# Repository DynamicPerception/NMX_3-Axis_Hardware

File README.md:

NMX_3-Axis_Hardware
===================

3-Axis version of the nanoMoCo controller with Bluetooth LE

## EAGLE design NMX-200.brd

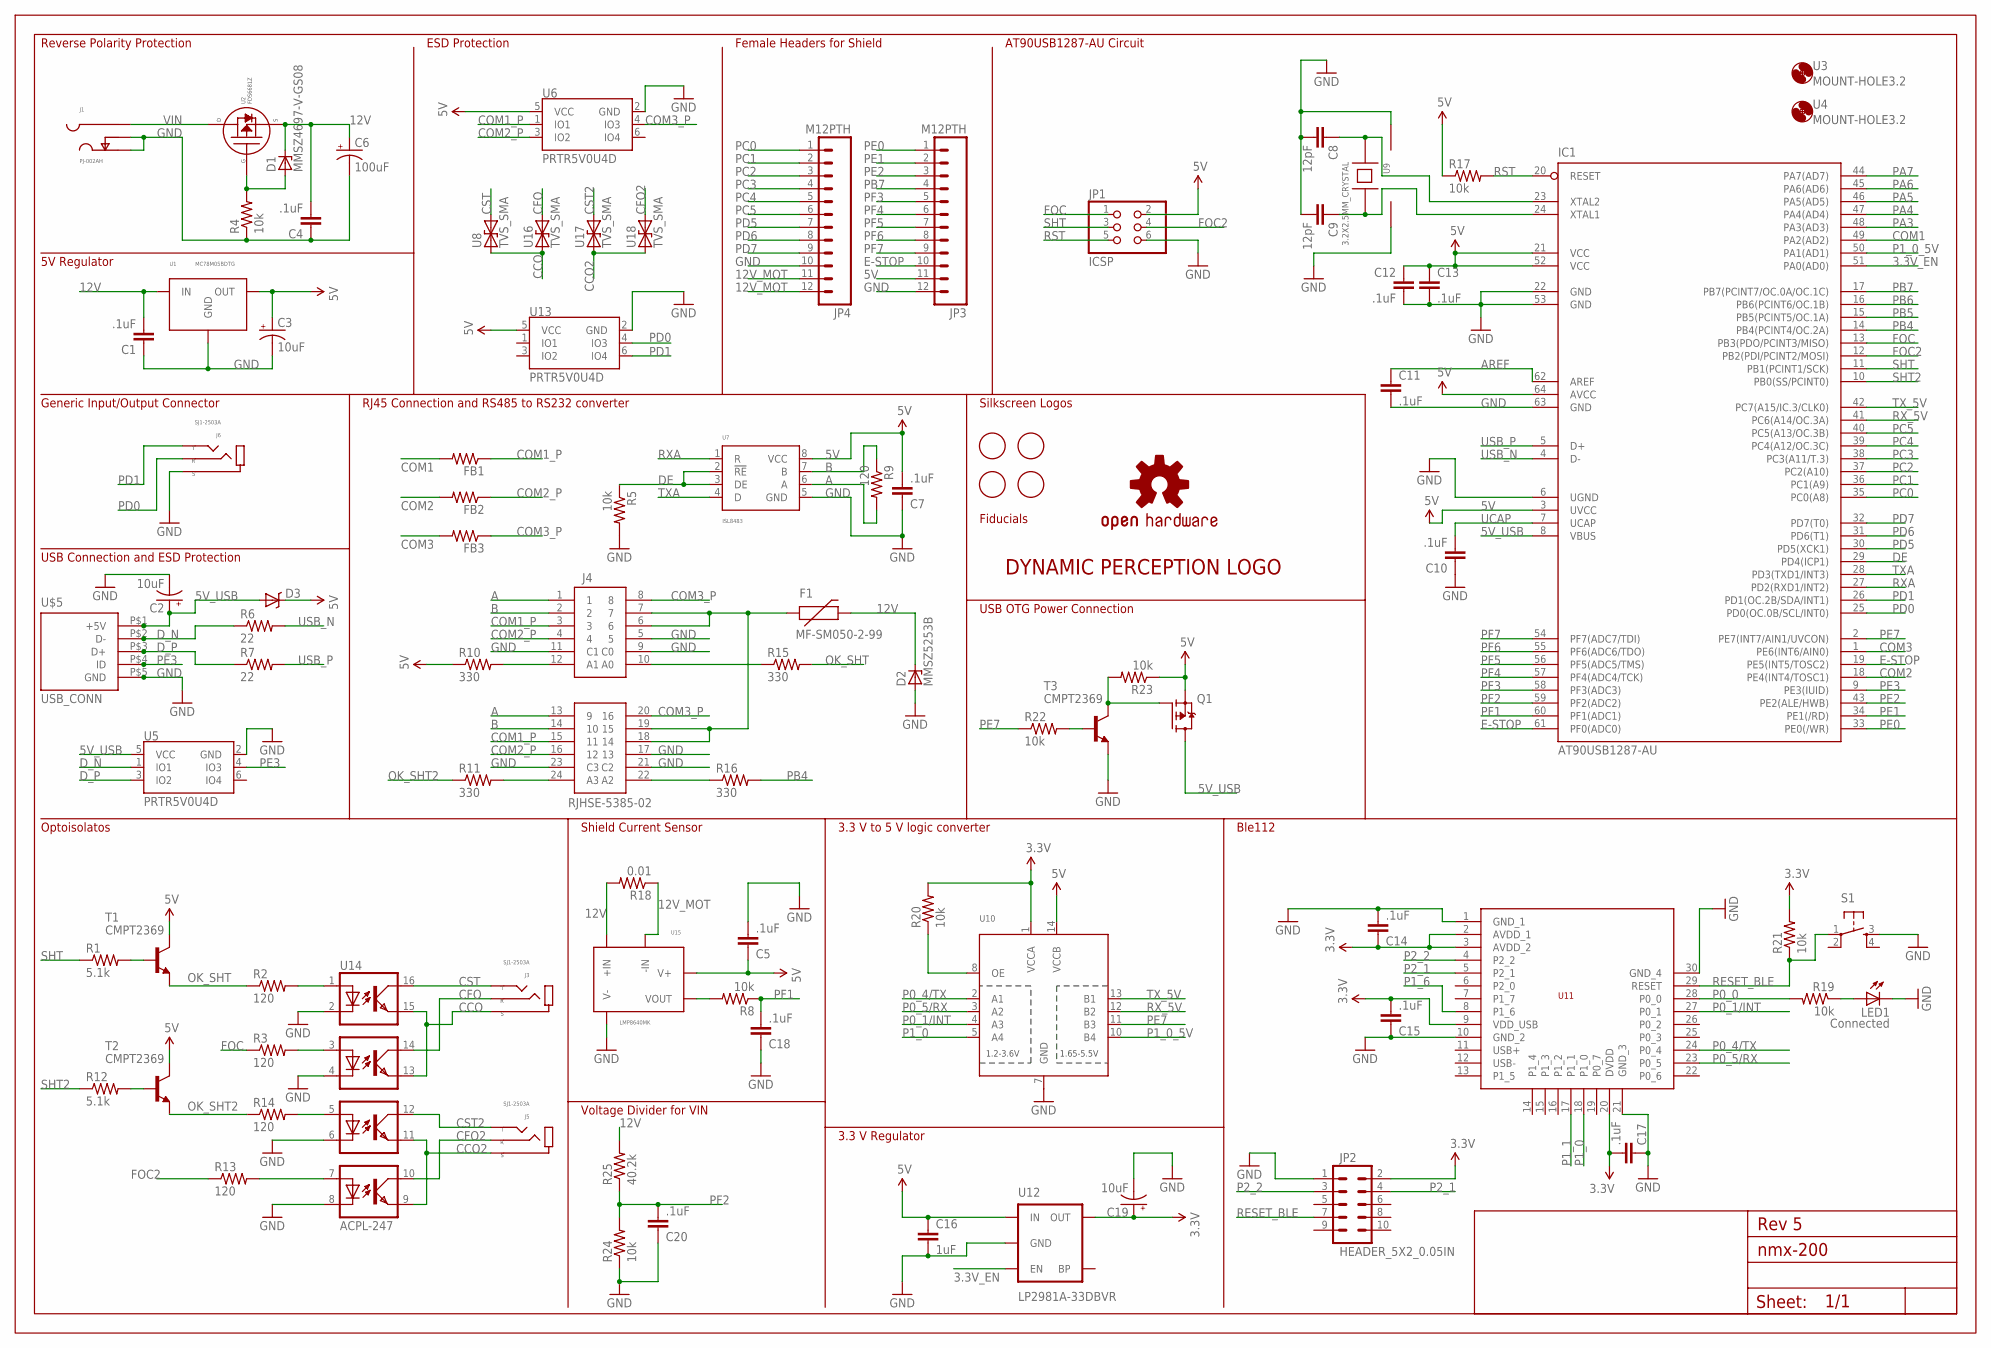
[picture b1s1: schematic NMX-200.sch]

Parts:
C1, C4, C5, C7, C10, C11, C12, C13, C14, C15, C17, C18, C20: .1uF; 0402-CAP; MPN TMK105BJ104KV-F
C2, C3, C19: 10uF; EIA3216; MPN T491A106M016AT
C6: 100uF; PANASONIC_D; MPN EEE-1EA101XP
C8, C9: 12pF; 0402-CAP; MPN C1005C0G1H120J050BA
C16: 1uF; 0402-CAP; MPN C1005X5R1C105K050BC
D1: MMSZ4697-V-GS08; SOD123; MPN MMSZ4697-E3-08
D2: MMSZ5253B; SOD123; MPN MMSZ5253B
D3: DIODE-SCHOTTKY-BAT20J; SOD-323; MPN PMEG3010BEA,115
F1: MF-SM050-2-99; PTC-2920; MPN 0ZCD0050FF2C
FB1, FB2, FB3: HZ0402B102R-10; R0402; MPN HZ0402B102R-10
FRAME2: A3L-LOCSILK_SCREEN; DRAWING_NAME
IC1: AT90USB1287-AU; TQFP64; MPN AT90USB1287-AU
J1: PJ-002AH; DC_JACK_KLDX; MPN PJ-002AH
J3, J5, J6: SJ1-2503A; MPN SJ1-2503A
J4: RJHSE-5385-02; MPN RJHSE-5385-02
JP1: ICSP; 2X03; MPN 67996-406HLF
JP2: HEADER_5X2_0.05IN; MPN 20021121-00010T4LF
JP3, JP4: M12PTH; 1X12; MPN PPTC121LFBN-RC
LED1: Connected; LED-0603; MPN LTST-S270TBKT
Q1: P-CHANNEL_MOSFET; SOT23-3; MPN FDV304P
R1, R12: 5.1k; R0402; MPN RC0402JR-075K1L
R2, R3, R13, R14: 120; R0402; MPN RC0402FR-07180RL
R4, R5, R8, R17, R20, R21, R22, R23, R24: 10k; R0402; MPN RC0402FR-0710KL
R6, R7: 22; R0402; MPN RC0402JR-0722RL
R9: 120; R0402; MPN RC0402JR-07120RL
R10, R11, R15, R16: 330; R0402; MPN RC0402FR-07330RL
R18: 0.01; R1206; MPN RLP73V2BR010JTD
R19: 10k; R0402; MPN RC0402FR-0714KL
R25: 40.2k; R0402; MPN RC0402FR-0740K2L
S1: TAC_SWITCH; TACTICLE_SWITCH_SMD_EVQP0_BOT; MPN EVQ-P0Q02Q
T1, T2: CMPT2369; SOT23-BEC; MPN 2SD1757KT146Q
T3: CMPT2369; SOT23-BEC; MPN BC847BMTF
U1: MC78M05BDTG; DPAK-3; MPN MC78M05BDTRKG
U2: FDS6681Z; DSO-8; MPN FDS6681Z
U3, U4: MOUNT-HOLE3.2; 3,2
U5, U6, U13: PRTR5V0U4D; SOT23-6; MPN PRTR5V0U4D
U7: ISL8483; SO-08; MPN SN65176BD
U8, U16, U17, U18: TVS_SMA; SMA_DIODE; MPN SMAJ48CA
U9: 3.2X2.5MM_CRYSTAL; 3.2X2.5MM; MPN CX3225SB16000E0FPZ25
U10: TXB0104PWR; TSSOP14; MPN TXB0104PWR
U11: BLE112; BLE112-A; MPN BLE112-A-V1
U12: LP2981A-33DBVR; SOT23-5; MPN LP2981A-33DBVR
U14: ACPL-247; 16-SOIC; MPN ACPL-247-500E
U15: LMP8640MK; 6-SOT; MPN LMP8640MK-H/NOPB
U$1: DP_LOGOMICRO; DP_LOGO_MICRO
U$2: OSHW-LOGOS; OSHW-LOGO-S
U$3, U$4, U$6, U$7: FIDUCIAL; FIDUCIAL_1MM
U$5: USB_CONN; 10118194-0001LF

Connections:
3.3V: C14.1, C15.2, C17.2, C19.A (+), JP2.2, R20.2, R21.2, U10.1 (VCCA), U11.2 (AVDD_1), U11.3 (AVDD_2), U11.9 (VDD_USB), U11.20 (DVDD), U12.5 (OUT)
3.3V_EN: IC1.51 (PA0(AD0)), U12.3 (EN)
5V: C3.A (+), C5.1, C7.2, C12.1, C13.1, C16.1, D3.C, IC1.3 (UVCC), IC1.21 (VCC), IC1.52 (VCC), IC1.64 (AVCC), JP1.2, JP3.11, Q1.S, R10.1, R17.1, R23.1, T1.C, T2.C, U1.2 (OUT), U6.5 (VCC), U7.8 (VCC), U10.14 (VCCB), U12.1 (IN), U13.5 (VCC), U15.6 (V+)
5V_USB: C2.A (+), D3.A, IC1.8 (VBUS), Q1.D, U5.5 (VCC), U$5.P$1 (+5V)
12V: C1.2, C4.2, C6.+, D1.C, D2.C, F1.P$2 (2), R18.2, R25.2, U1.1 (IN), U2.1 (SOURCE), U2.2 (SOURCE), U2.3 (SOURCE), U15.3 (+IN)
12V_MOT: JP4.11, JP4.12, R18.1, U15.4 (-IN)
A: J4.1, J4.13 (9), R9.2, U7.6 (A)
AREF: C11.1, IC1.62 (AREF)
B: J4.2, J4.14 (10), R9.1, U7.7 (B)
CCO: J3.1 (S), U8.C (1), U14.13, U14.15, U16.C (1)
CCO2: J5.1 (S), U14.9, U14.11, U17.C (1), U18.C (1)
CFO: J3.4 (R), U14.14, U16.A (2)
CFO2: J5.4 (R), U14.10, U18.A (2)
COM1: FB1.2, IC1.49 (PA2(AD2))
COM1_P: FB1.1, J4.3, J4.15 (11), U6.1 (IO1)
COM2: FB2.2, IC1.18 (PE4(INT4/TOSC1))
COM2_P: FB2.1, J4.4, J4.16 (12), U6.3 (IO2)
COM3: FB3.2, IC1.1 (PE6(INT6/AIN0))
COM3_P: FB3.1, J4.8, J4.20 (16), U6.4 (IO3)
CST: J3.2 (T), J3.3 (T), U8.A (2), U14.16
CST2: J5.2 (T), J5.3 (T), U14.12, U17.A (2)
DE: IC1.29 (PD4(ICP1)), R5.1, U7.2 (!RE), U7.3 (DE)
D_N: R6.1, U5.1 (IO1), U$5.P$2 (D-)
D_P: R7.1, U5.3 (IO2), U$5.P$3 (D+)
E-STOP: IC1.19 (PE5(INT5/TOSC2)), IC1.61 (PF0(ADC0)), JP3.10
FOC: IC1.13 (PB3(PDO/PCINT3/MISO)), JP1.1, R3.1
FOC2: IC1.12 (PB2(PDI/PCINT2/MOSI)), JP1.4, R13.1
GND: C1.1, C2.C (-), C3.C (-), C4.1, C5.2, C6.-, C7.1, C8.2, C9.2, C10.1, C11.2, C12.2, C13.2, C14.2, C15.1, C16.2, C17.1, C18.1, C19.C (-), C20.1, D2.A, IC1.6 (UGND), IC1.22 (GND), IC1.53 (GND), IC1.63 (GND), J1.GND (SLEEVE), J1.GNDBREAK (SLEEVE_SHUNT), J4.5, J4.9 (C0), J4.11 (C1), J4.17 (13), J4.21 (C2), J4.23 (C3), J6.1 (S), JP1.6, JP2.1, JP3.12, JP4.10, LED1.C, R4.1, R5.2, R24.1, S1.3, T3.E, U1.4 (GND), U5.2 (GND), U6.2 (GND), U7.5 (GND), U9.2 (GND), U9.4, U10.7 (GND), U11.1 (GND_1), U11.10 (GND_2), U11.21 (GND_3), U11.30 (GND_4), U12.2 (GND), U13.2 (GND), U14.2, U14.4, U14.6, U14.8, U15.2 (V-), U$5.P$5 (GND)
unnamed: R20.1, U10.8 (OE)
unnamed: R22.2, T3.B
unnamed: LED1.A, R19.1
unnamed: J4.10 (A0), R15.1
unnamed: D1.A, R4.2, U2.4 (GATE)
unnamed: R2.2, U14.1
unnamed: R3.2, U14.3
unnamed: R8.2, U15.1 (VOUT)
unnamed: R14.2, U14.5
unnamed: R13.2, U14.7
unnamed: J4.12 (A1), R10.2
unnamed: J4.24 (A3), R11.2
unnamed: Q1.G, R23.2, T3.C
unnamed: J4.22 (A2), R16.1
unnamed: F1.P$1 (1), J4.6, J4.7, J4.18 (14), J4.19 (15)
unnamed: R1.2, T1.B
unnamed: R12.2, T2.B
OK_SHT: R2.1, R15.2, T1.E
OK_SHT2: R11.1, R14.1, T2.E
P0_0: R19.2, U11.28 (P0_0)
P0_1/INT: U10.4 (A3), U11.27 (P0_1)
P0_4/TX: U10.2 (A1), U11.24 (P0_4)
P0_5/RX: U10.3 (A2), U11.23 (P0_5)
P1_0: U10.5 (A4), U11.18 (P1_0)
P1_0_5V: IC1.50 (PA1(AD1)), U10.10 (B4)
P1_1: U11.17 (P1_1)
P1_6: U11.8 (P1_6)
P2_1: JP2.4, U11.5 (P2_1)
P2_2: JP2.3, U11.4 (P2_2)
PA3: IC1.48 (PA3(AD3))
PA4: IC1.47 (PA4(AD4))
PA5: IC1.46 (PA5(AD5))
PA6: IC1.45 (PA6(AD6))
PA7: IC1.44 (PA7(AD7))
PB4: IC1.14 (PB4(PCINT4/OC.2A)), R16.2
PB5: IC1.15 (PB5(PCINT5/OC.1A))
PB6: IC1.16 (PB6(PCINT6/OC.1B))
PB7: IC1.17 (PB7(PCINT7/OC.0A/OC.1C)), JP3.4
PC0: IC1.35 (PC0(A8)), JP4.1
PC1: IC1.36 (PC1(A9)), JP4.2
PC2: IC1.37 (PC2(A10)), JP4.3
PC3: IC1.38 (PC3(A11/T.3)), JP4.4
PC4: IC1.39 (PC4(A12/OC.3C)), JP4.5
PC5: IC1.40 (PC5(A13/OC.3B)), JP4.6
PD0: IC1.25 (PD0(OC.0B/SCL/INT0)), J6.4 (R), U13.4 (IO3)
PD1: IC1.26 (PD1(OC.2B/SDA/INT1)), J6.2 (T), J6.3 (T), U13.6 (IO4)
PD5: IC1.30 (PD5(XCK1)), JP4.7
PD6: IC1.31 (PD6(T1)), JP4.8
PD7: IC1.32 (PD7(T0)), JP4.9
PE0: IC1.33 (PE0(/WR)), JP3.1
PE1: IC1.34 (PE1(/RD)), JP3.2
PE2: IC1.43 (PE2(ALE/HWB)), JP3.3
PE3: IC1.9 (PE3(IUID)), U5.4 (IO3), U$5.P$4 (ID)
PE7: IC1.2 (PE7(INT7/AIN1/UVCON)), R22.1, U10.11 (B3)
PF1: C18.2, IC1.60 (PF1(ADC1)), R8.1
PF2: C20.2, IC1.59 (PF2(ADC2)), R24.2, R25.1
PF3: IC1.58 (PF3(ADC3)), JP3.5
PF4: IC1.57 (PF4(ADC4/TCK)), JP3.6
PF5: IC1.56 (PF5(ADC5/TMS)), JP3.7
PF6: IC1.55 (PF6(ADC6/TDO)), JP3.8
PF7: IC1.54 (PF7(ADC7/TDI)), JP3.9
RESET_BLE: JP2.7, R21.1, S1.1, U11.29 (RESET)
RST: IC1.20 (RESET), JP1.5, R17.2
RXA: IC1.27 (PD2(RXD1/INT2)), U7.1 (R)
RX_5V: IC1.41 (PC6(A14/OC.3A)), U10.12 (B2)
SHT: IC1.11 (PB1(PCINT1/SCK)), JP1.3, R1.1
SHT2: IC1.10 (PB0(SS/PCINT0)), R12.1
TXA: IC1.28 (PD3(TXD1/INT3)), U7.4 (D)
TX_5V: IC1.42 (PC7(A15/IC.3/CLK0)), U10.13 (B1)
UCAP: C10.2, IC1.7 (UCAP)
USB_N: IC1.4 (D-), R6.2
USB_P: IC1.5 (D+), R7.2
VIN: J1.PWR (PIN), U2.5 (DRAIN), U2.6 (DRAIN), U2.7 (DRAIN), U2.8 (DRAIN)
XTAL1: C9.1, IC1.24 (XTAL1), U9.3
XTAL2: C8.1, IC1.23 (XTAL2), U9.1

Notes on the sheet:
Ble112
3.3 V to 5 V logic converter
3.3 V Regulator
Optoisolatos
Reverse Polarity Protection
5V Regulator
Generic Input/Output Connector
USB Connection and ESD Protection
RJ45 Connection and RS485 to RS232 converter
ESD Protection
Female Headers for Shield
AT90USB1287-AU Circuit
Shield Current Sensor
Voltage Divider for VIN
USB OTG Power Connection
Silkscreen Logos
Fiducials
Rev 5

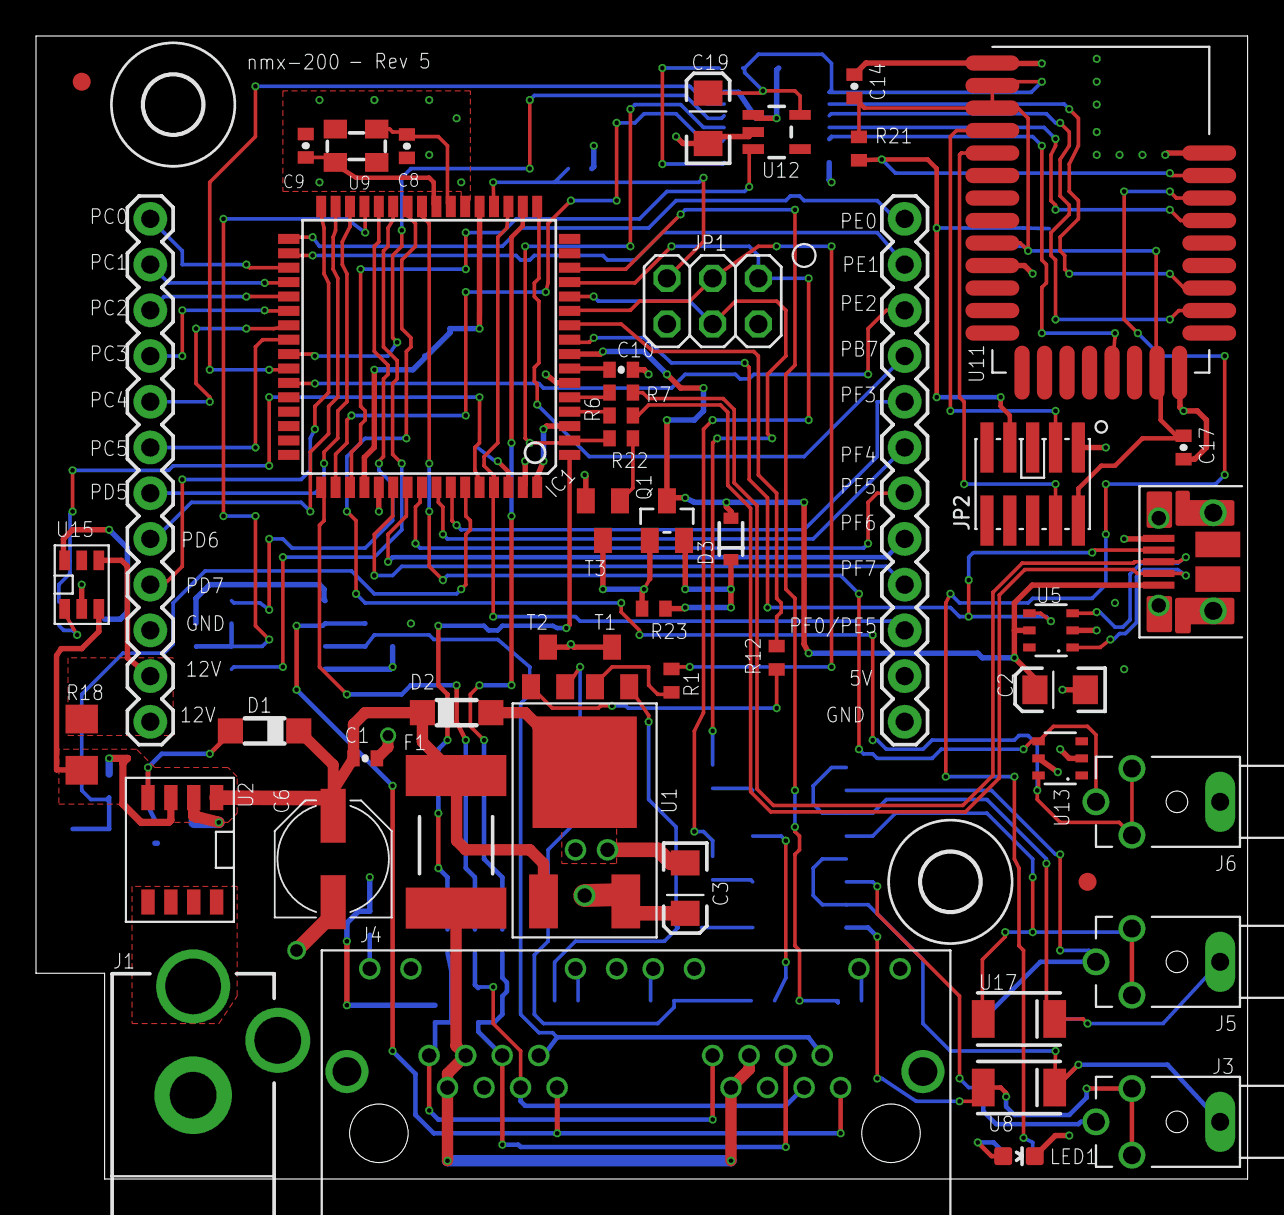
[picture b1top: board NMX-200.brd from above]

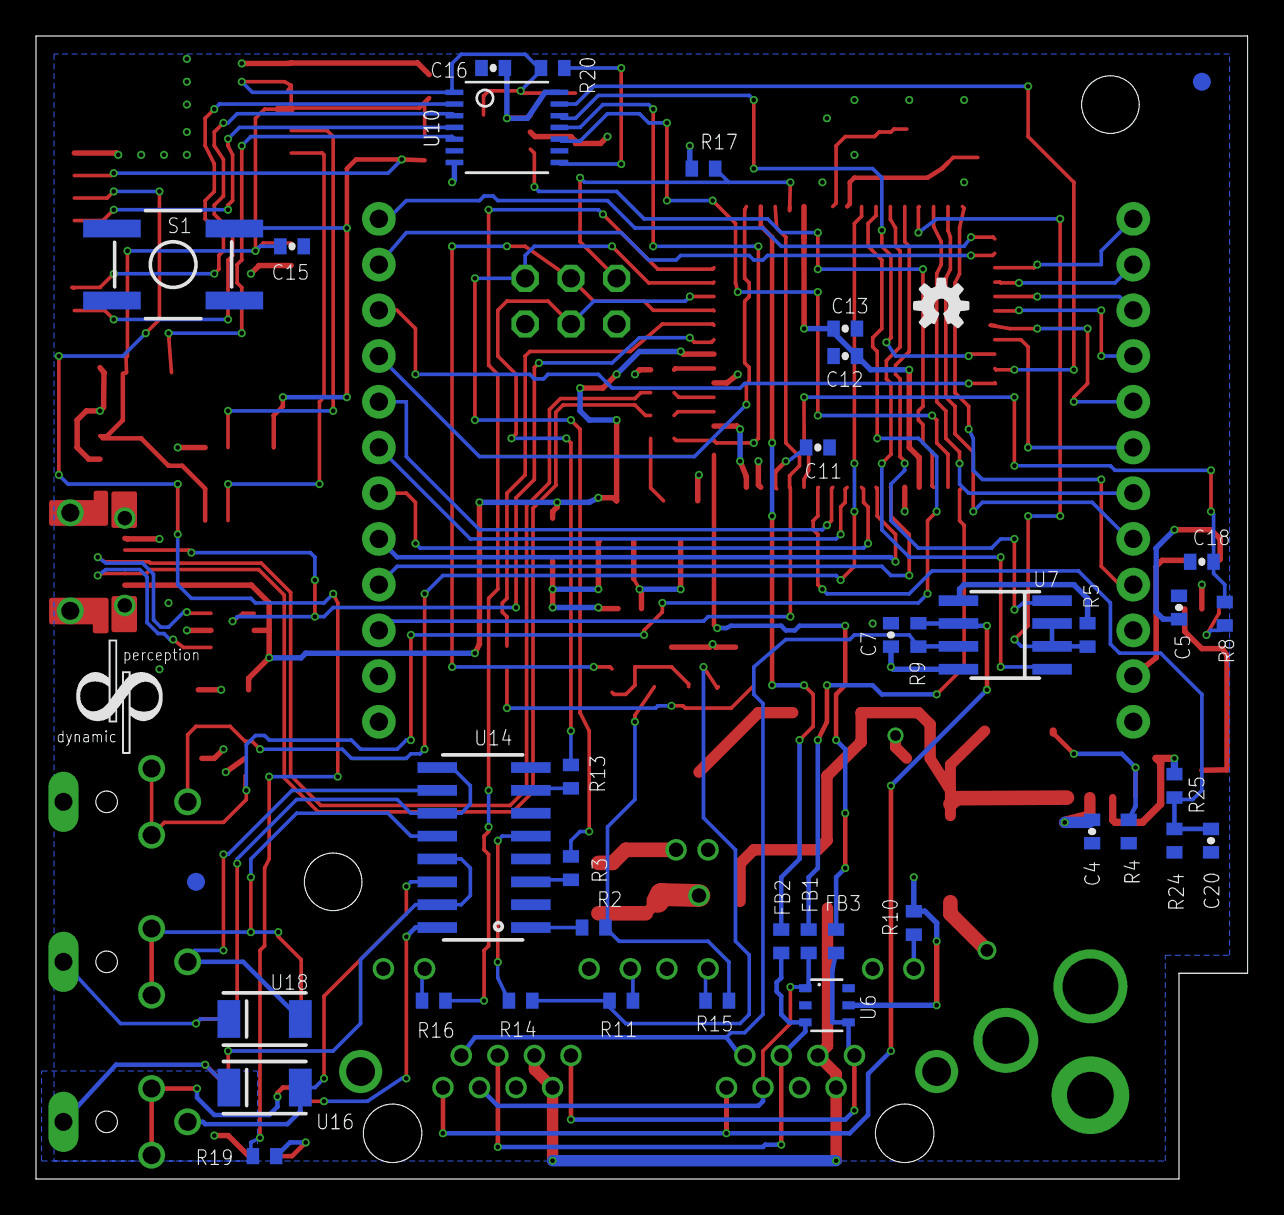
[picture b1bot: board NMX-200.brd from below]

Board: 4 copper layers, 67.3 x 63.5 mm, 94 parts (40 on the bottom side), 94 nets.

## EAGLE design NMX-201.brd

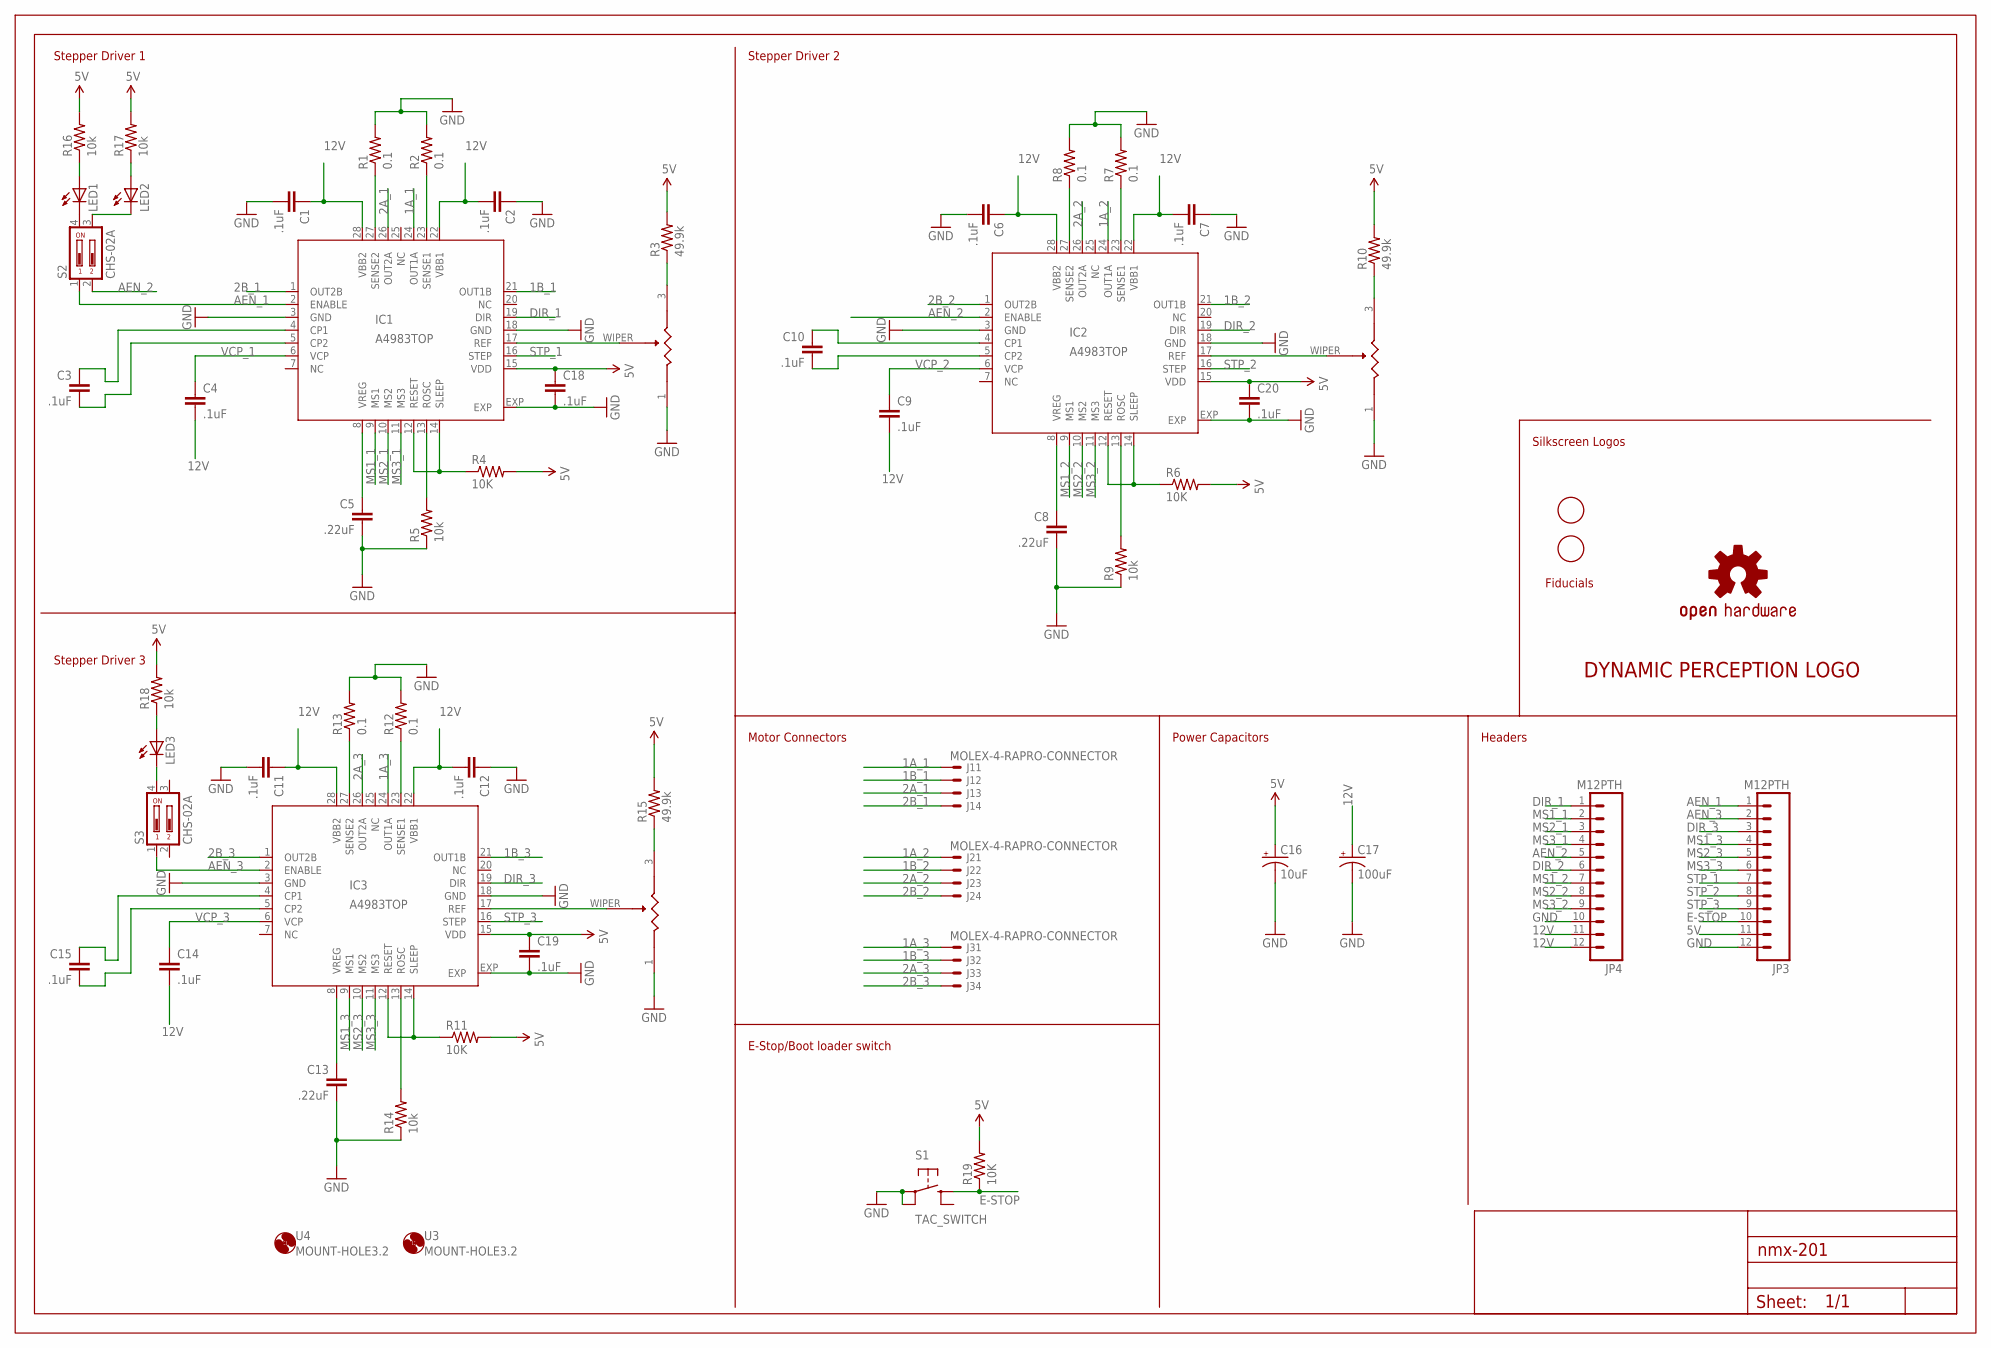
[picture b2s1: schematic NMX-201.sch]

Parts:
C1, C2, C3, C4, C6, C7, C9, C10, C11, C12, C14, C15, C18, C19, C20: .1uF; 0402-CAP; MPN TMK105BJ104KV-F
C5, C8, C13: .22uF; 0402-CAP; MPN TMK105BJ224KVHF
C16: 10uF; EIA3216; MPN T491A106M016AT
C17: 100uF; PANASONIC_D; MPN EEE-1EA101XP
FRAME2: A3L-LOCSILK_SCREEN; DRAWING_NAME
IC1, IC2, IC3: A4983TOP; QFN28ET; MPN A4983SETTR-T
J1, J2, J3: MOLEX-4-RAPRO-CONNECTOR; PRO_CONNECTOR; MPN 0022053041
JP3, JP4: M12PTH; 1X12; MPN 0901200132
LED1, LED2, LED3: LED0603; LED-0603; MPN LB Q39G-L2N2-35-1
R1, R2, R7, R8, R12, R13: 0.1; R0603; MPN RU1608FR100CS
R3, R10, R15: 49.9k; R0402_BOTTOM; MPN RC0402FR-0749K9L
R4, R6, R11, R19: 10K; R0402_BOTTOM; MPN RC0402FR-0710KL
R5, R9, R14: 10k; R0402_BOTTOM; MPN RC0402FR-0720KL
R16, R17, R18: 10k; R0402_BOTTOM; MPN RC0402FR-0714KL
S1: TAC_SWITCH; TAC_SWITCH_THR; MPN 2-1825027-0
S2, S3: CHS-02A
U1, U2, U5: CADJ; 3MM_SMD; MPN TC33X-2-103E
U3, U4: MOUNT-HOLE3.2; 3,2
U$1: DP_LOGOMICRO; DP_LOGO_MICRO
U$2: OSHW-LOGOS; OSHW-LOGO-S
U$3, U$4: FIDUCIAL; FIDUCIAL_1MM

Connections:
1A_1: IC1.24 (OUT1A), J1.P$1
1A_2: IC2.24 (OUT1A), J2.P$1
1A_3: IC3.24 (OUT1A), J3.P$1
1B_1: IC1.21 (OUT1B), J1.P$2
1B_2: IC2.21 (OUT1B), J2.P$2
1B_3: IC3.21 (OUT1B), J3.P$2
2A_1: IC1.26 (OUT2A), J1.P$3
2A_2: IC2.26 (OUT2A), J2.P$3
2A_3: IC3.26 (OUT2A), J3.P$3
2B_1: IC1.1 (OUT2B), J1.P$4
2B_2: IC2.1 (OUT2B), J2.P$4
2B_3: IC3.1 (OUT2B), J3.P$4
5V: C16.A (+), C18.1, C19.1, C20.1, IC1.15 (VDD), IC2.15 (VDD), IC3.15 (VDD), JP3.11, R3.2, R4.2, R6.2, R10.2, R11.2, R15.2, R16.2, R17.2, R18.2, R19.2
12V: C1.1, C2.2, C4.2, C6.1, C7.2, C9.2, C11.1, C12.2, C14.2, C17.+, IC1.22 (VBB1), IC1.28 (VBB2), IC2.22 (VBB1), IC2.28 (VBB2), IC3.22 (VBB1), IC3.28 (VBB2), JP4.11, JP4.12
AEN_1: IC1.2 (ENABLE), JP3.1, S2.1
AEN_2: IC2.2 (ENABLE), JP4.5, S2.2
AEN_3: IC3.2 (ENABLE), JP3.2, S3.1
ARST1: IC1.12 (RESET), IC1.14 (SLEEP), R4.1
ARST2: IC2.12 (RESET), IC2.14 (SLEEP), R6.1
ARST3: IC3.12 (RESET), IC3.14 (SLEEP), R11.1
DIR_1: IC1.19 (DIR), JP4.1
DIR_2: IC2.19 (DIR), JP4.6
DIR_3: IC3.19 (DIR), JP3.3
E-STOP: JP3.10, R19.1, S1.B (3)
GND: C1.2, C2.1, C5.2, C6.2, C7.1, C8.2, C11.2, C12.1, C13.2, C16.C (-), C17.-, C18.2, C19.2, C20.2, IC1.3 (GND), IC1.18 (GND), IC1.EXP, IC2.3 (GND), IC2.18 (GND), IC2.EXP, IC3.3 (GND), IC3.18 (GND), IC3.EXP, JP3.12, JP4.10, R1.2, R2.2, R5.1, R7.2, R8.2, R9.1, R12.2, R13.2, R14.1, S1.A (1), S1.P$1 (2), U1.1, U2.1, U5.1
MS1_1: IC1.9 (MS1), JP4.2
MS1_2: IC2.9 (MS1), JP4.7
MS1_3: IC3.9 (MS1), JP3.4
MS2_1: IC1.10 (MS2), JP4.3
MS2_2: IC2.10 (MS2), JP4.8
MS2_3: IC3.10 (MS2), JP3.5
MS3_1: IC1.11 (MS3), JP4.4
MS3_2: IC2.11 (MS3), JP4.9
MS3_3: IC3.11 (MS3), JP3.6
unnamed: C10.1, IC2.4 (CP1)
unnamed: C10.2, IC2.5 (CP2)
unnamed: IC2.23 (SENSE1), R7.1
unnamed: IC2.27 (SENSE2), R8.1
unnamed: IC2.17 (REF), U2.WIPER (2)
unnamed: R10.1, U2.3
unnamed: C15.1, IC3.4 (CP1)
unnamed: C15.2, IC3.5 (CP2)
unnamed: IC3.23 (SENSE1), R12.1
unnamed: IC3.27 (SENSE2), R13.1
unnamed: IC3.17 (REF), U5.WIPER (2)
unnamed: R15.1, U5.3
unnamed: LED1.A, R16.1
unnamed: LED2.A, R17.1
unnamed: LED3.A, R18.1
unnamed: LED1.C, S2.4
unnamed: LED2.C, S2.3
unnamed: LED3.C, S3.4
unnamed: C3.1, IC1.4 (CP1)
unnamed: C3.2, IC1.5 (CP2)
unnamed: IC1.23 (SENSE1), R2.1
unnamed: IC1.27 (SENSE2), R1.1
unnamed: IC1.17 (REF), U1.WIPER (2)
unnamed: R3.1, U1.3
ROSC1: IC1.13 (ROSC), R5.2
ROSC2: IC2.13 (ROSC), R9.2
ROSC3: IC3.13 (ROSC), R14.2
STP_1: IC1.16 (STEP), JP3.7
STP_2: IC2.16 (STEP), JP3.8
STP_3: IC3.16 (STEP), JP3.9
VCP_1: C4.1, IC1.6 (VCP)
VCP_2: C9.1, IC2.6 (VCP)
VCP_3: C14.1, IC3.6 (VCP)
VREG1: C5.1, IC1.8 (VREG)
VREG2: C8.1, IC2.8 (VREG)
VREG3: C13.1, IC3.8 (VREG)

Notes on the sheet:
Stepper Driver 1
Stepper Driver 2
Stepper Driver 3
Motor Connectors
E-Stop/Boot loader switch
Headers
Power Capacitors
Silkscreen Logos
Fiducials

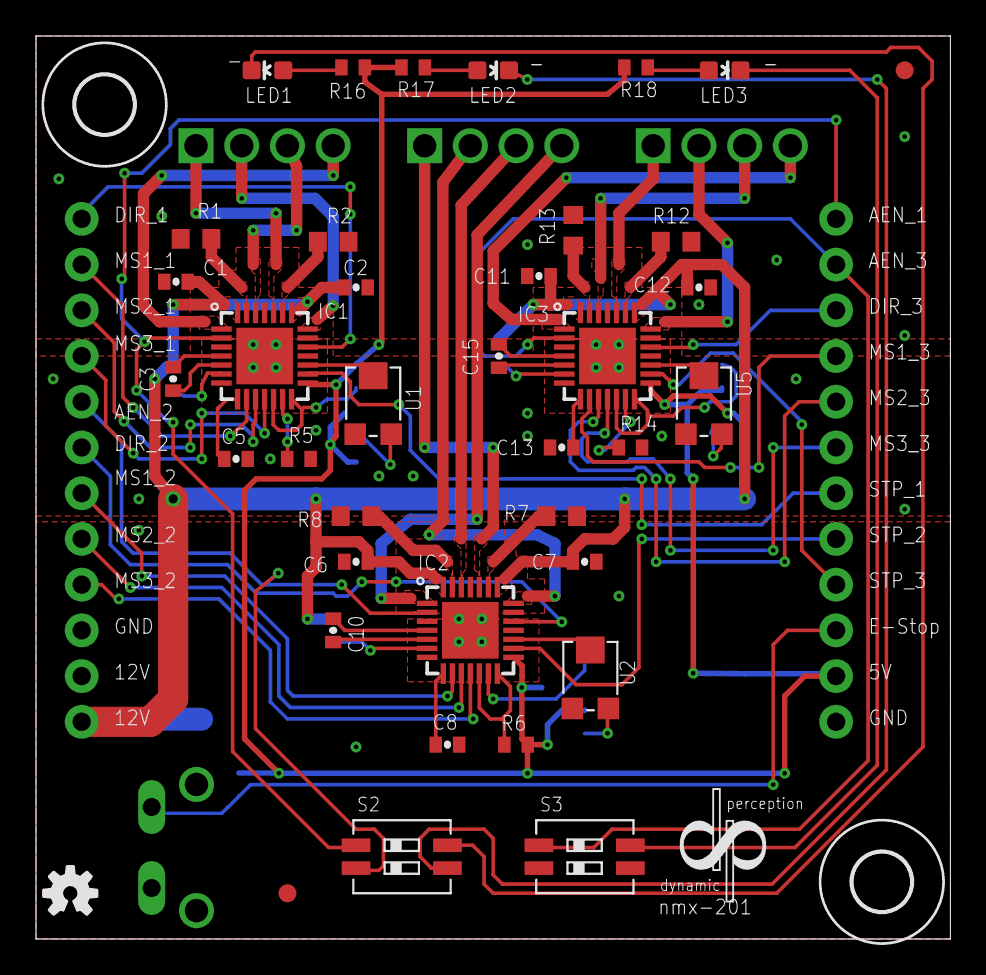
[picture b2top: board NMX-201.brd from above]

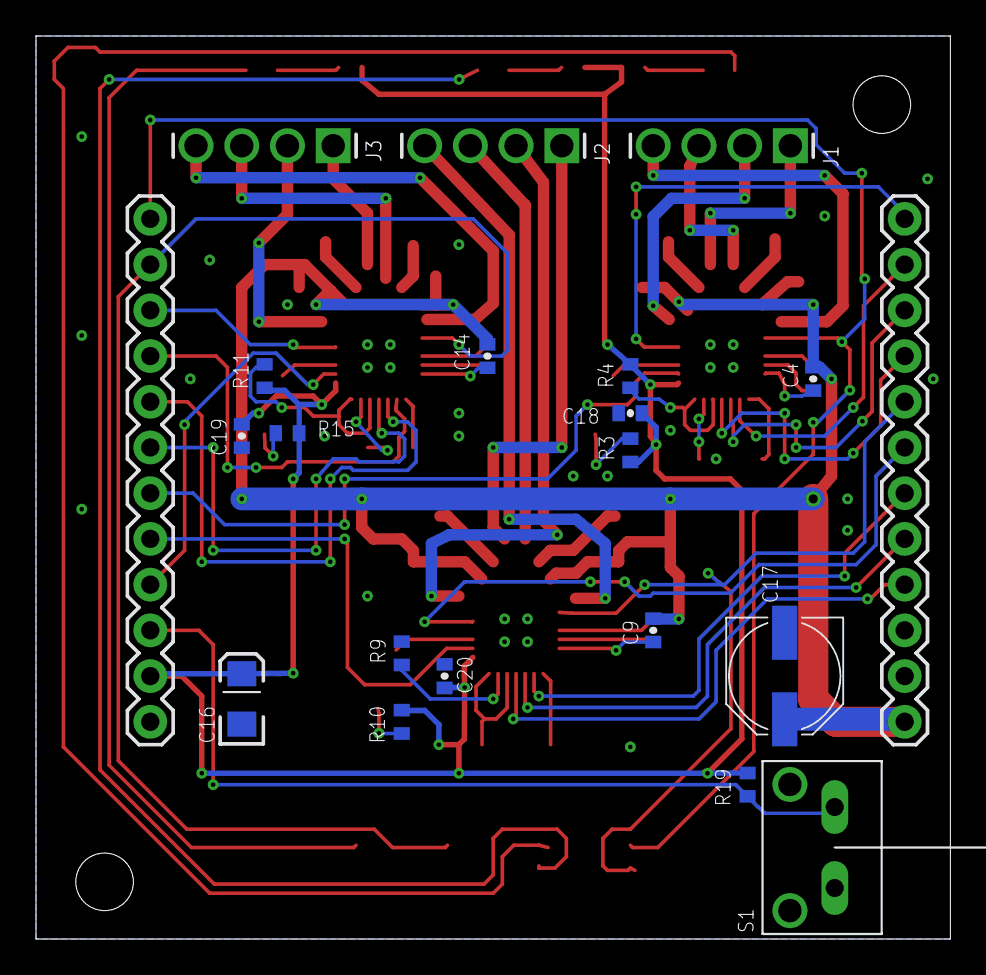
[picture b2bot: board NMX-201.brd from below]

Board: 2 copper layers, 50.8 x 50.2 mm, 63 parts (20 on the bottom side), 70 nets.

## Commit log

2014-08-26 Initial GitHub upload - 8/26/14
    To do:
    --Update ESD suppressors on phototransistors from 5V to 80V limit.
    --Change trace width from .024 to .025 on all traces from motor headers
2014-08-27 Board Updates
    Changed TVS diodes for isolated jack for 200, changed a few traces in
    201
2014-08-27 Added .gitignore
    Ignores backup files and CAM files. If you want to upload CAM files, zip
    them first and upload them as a bundle.
2014-08-27 Deleted backup files that should have been ignored
2014-08-27 Updated TVS Attributes
2014-08-27 Fixed NMX-200 schematic typo
    Two 10k resistors were marked with an upper case "K" instead of lower
    case k", which caused them to appear as a separate line on the exported
    BOM.
2014-08-27 Upload of fabrication data
    Upload of ZIP files containing Gerber files, BOMs, and assembly drawings
    for each board.
2014-08-27 Fixed fabrication data upload
    Accidentally uploaded the NMX-200 CAM zip instead of the NMX-201
    fabrication zip. Also unzipped everything in those files and put them in
    normal folders.
2014-08-27 Removed extraneous zip files
    Oops, forgot to remove these
2014-09-30 Changed silkscreen to indicate polarity of some components
2014-10-03 Update to Silk Screen
2014-10-03 Update Silk Screen
2015-01-23 Replaced 5V regulator with cold-resistant model
    The MC78M05CDTG ON-Semiconductor regulator was replaced with the
    MC78M05BDTG. The minimum operating temperature of former is 0°C and the
    latter is -45°C. There have been issues connecting to the NMX via
    Bluetooth when it is very cold, so this change is being made in an
    attempt to address that issue.
    The CAM files have not changed at all, but their names have been updated
2016-03-18 Added NMX-201-B
2016-03-18 Added NMX-200 and NMX-201 schematic PDFs
2016-08-18 Changed NMX 200 to 4 layer design
2016-08-19 Fixed broken route, moved oscilator caps to top layer
2016-08-23 Added DIP switches and increased LED resistor vals
    NMX 201-B:
    - Added switches to allow users to turn off motor movement indicator
    LEDs.
    - Changed R16, R17, R19 to 14k resistances in order to reduce LED
    brightness.
2016-08-23 Updated NMX-201 to match NMX-201B
    The only difference between NMX-201 and NMX-201B is whether the the
    component attached to the motor connector ports is a screw terminal or a
    Molex connector, so there's really no need to maintain two different
    schematics / board files. These differences should be reflected in the
    BOM instead.
2016-08-29 Fixed DRC errors
2016-09-15 Moved USB connector, fixed DRC errors
    Moved the connector slightly closer to the edge of the board and updated
    part with revised library part that addresses DRC errors.
2016-09-15 Tented vias
    Changed DRC rules to not add stop mask to vias.
2016-09-16 Fixed incomplete board outline
2016-09-16 Added copper plane clearance from board edge
2016-09-16 Added fiducials to bottom of NMX-200
2016-11-21 Removed lock files
2016-11-21 Updated .gitignore
2016-11-21 Updated project file
2016-11-21 Removed NMX-201-B files
    The PCB is identical for the 201 and 201-B boards, only the connector
    part is different. No need to maintain two different Eagle files.
2016-12-15 Fixed some ERC errors, switched to OSHPark DRC
2016-12-15 Added "Rev 5" silkscreen marker
2016-12-15 Changed several resistor values to reduce unique part count
    See NMX-200 / NMX-201 BOM Google doc change log for 12/15/16 for
    details.
2017-01-19 Updated .gitignore to exclude CAM files
2017-01-19 Rev 3 BOM update
2017-01-19 Added via tenting
2017-01-19 Corrected header silk screen labels
2017-01-27 Increased copper pour isolation, fixed DC jack holes
    On the first prototype boards, a manufacturing defect caused the ground
    plane to make contact with one of the via pads, causing a very difficult
    to identify problem with BLE connectivity. The clearance between both
    GND and 5V copper pours and traces, vias, and pads has been increased to
    avoid this in the future.
    The drill holes for the DC jack were just a bit too small, so they have
2017-02-01 TEST COMMIT

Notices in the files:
parts and their libraries:
SparkFun-Capacitors: Licensing: Creative Commons ShareAlike 4.0 International - https://creativecommons.org/licenses/by-sa/4.0
